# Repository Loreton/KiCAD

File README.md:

KiCAD
=====

Progetti realizzati con KiCad

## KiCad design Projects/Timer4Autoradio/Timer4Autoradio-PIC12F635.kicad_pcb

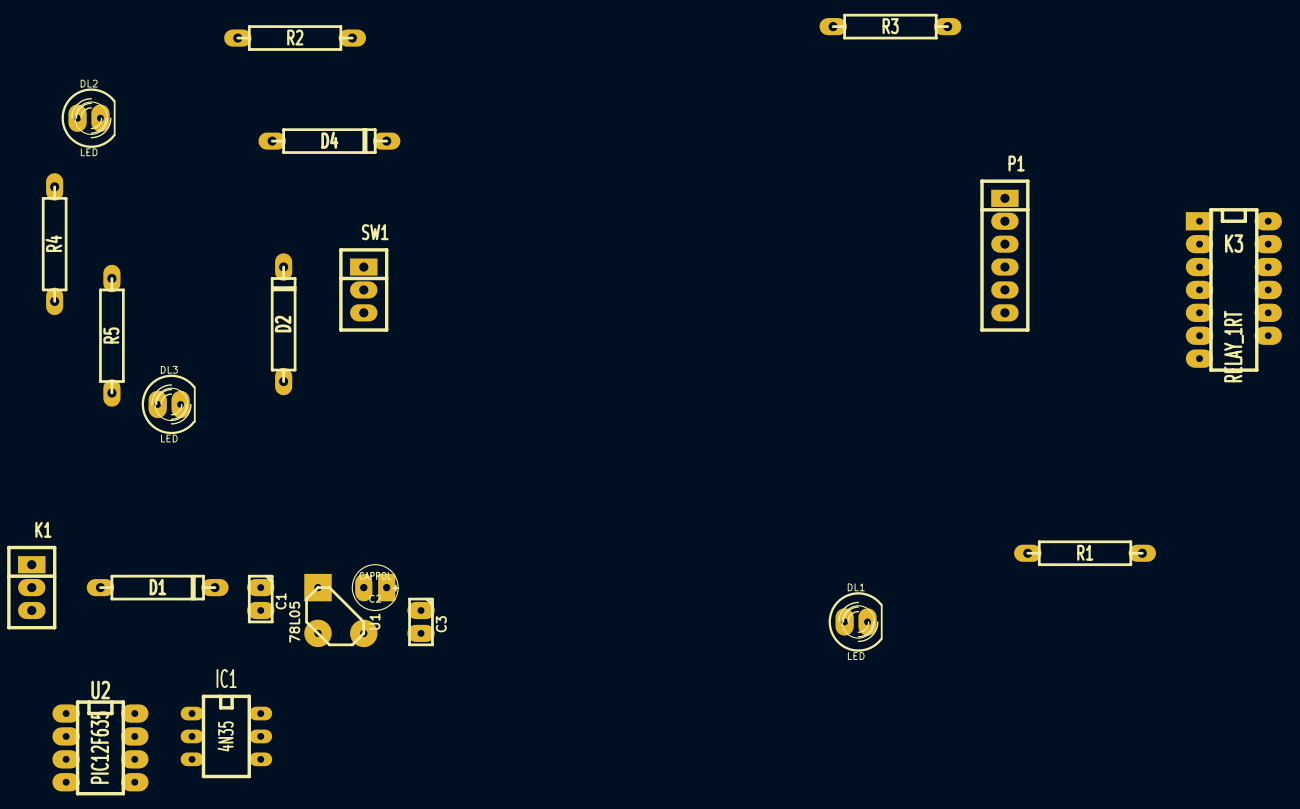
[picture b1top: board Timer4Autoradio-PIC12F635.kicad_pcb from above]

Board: 2 copper layers, 21 parts (0 on the bottom side), 17 nets, no tracks yet.

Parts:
C1, C3: C; Cap_100
C2: CAPPOL; CAPE_100_V5
D1: 1N4001; Diode_500
D2: 1N4148; Diode_500
D4: DIODE; Diode_500
DL1, DL2, DL3: LED; LED-5MM
IC1: 4N35; DIP-6_300
K1: 12Vcc; SIP-03
K3: RELAY_1RT; DIP-14_300
P1: CONN_06; SIP-06
R1: 27K; Res-500
R2: 100K; Res-500
R3: 25K; Res-500
R4: 470; Res-500
R5: 470K; Res-500
SW1: Power; SIP-03
U1: 78L05; LM78XX-TO92-ELL
U2: PIC12F635; DIP-8_300

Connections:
+5V: D2.2, R3.1, U2.1
+12V: D1.1, D4.2, DL1.1, K1.2, K3.8
/Out: R4.2, U2.3
GND: C1.2, C2.2, C3.2, DL3.2, IC1.2, IC1.4, K1.3, P1.3, R2.2, SW1.1, U1.GND, U2.8
ICSPCLK: P1.5, U2.6
ICSPDAT: P1.4, U2.7
unnamed: DL2.2, IC1.1
unnamed: DL2.1, R4.1
unnamed: D4.1, DL1.2, IC1.5, K3.9
unnamed: C2.1, C3.1, D2.1, U1.VO
unnamed: C1.1, D1.2, U1.VI
unnamed: K1.1, R1.1
unnamed: IC1.6, R1.2, R2.1
unnamed: R5.2, U2.2
unnamed: SW1.2, U2.5
unnamed: DL3.1, R5.1
VPP/MCLR: P1.1, R3.2, U2.4

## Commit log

2014-04-30 starting project
2014-05-05 inizio studio del prodotto
2014-07-11 modificato Tilt-PIC12F635
2014-09-25 Sirena con relè
2014-11-16 November 16, 2014
2014-11-18 2014-11-18 07:10 - Automatic commit
2014-11-18 2014-11-18 07:38 - Automatic commit
2014-11-18 2014-11-18 08:06 - commit with no comment
2014-11-19 2014-11-19 20:41 - commit with no comment
2014-11-29 2014-11-29 09:31 - commit with no comment
2014-11-29 2014-11-29 21:44 - commit with no comment
2014-11-30 2014-11-30 21:10 - commit with no comment
2014-12-14 2014-12-14 20:33 - commit with no comment
2015-02-06 2015-02-06 07:53 - commit with no comment
2015-02-10 spostati i progetti ad un livello esterno al KiCad
2017-02-28 2017-02-28 07:49 - commit with no comment
